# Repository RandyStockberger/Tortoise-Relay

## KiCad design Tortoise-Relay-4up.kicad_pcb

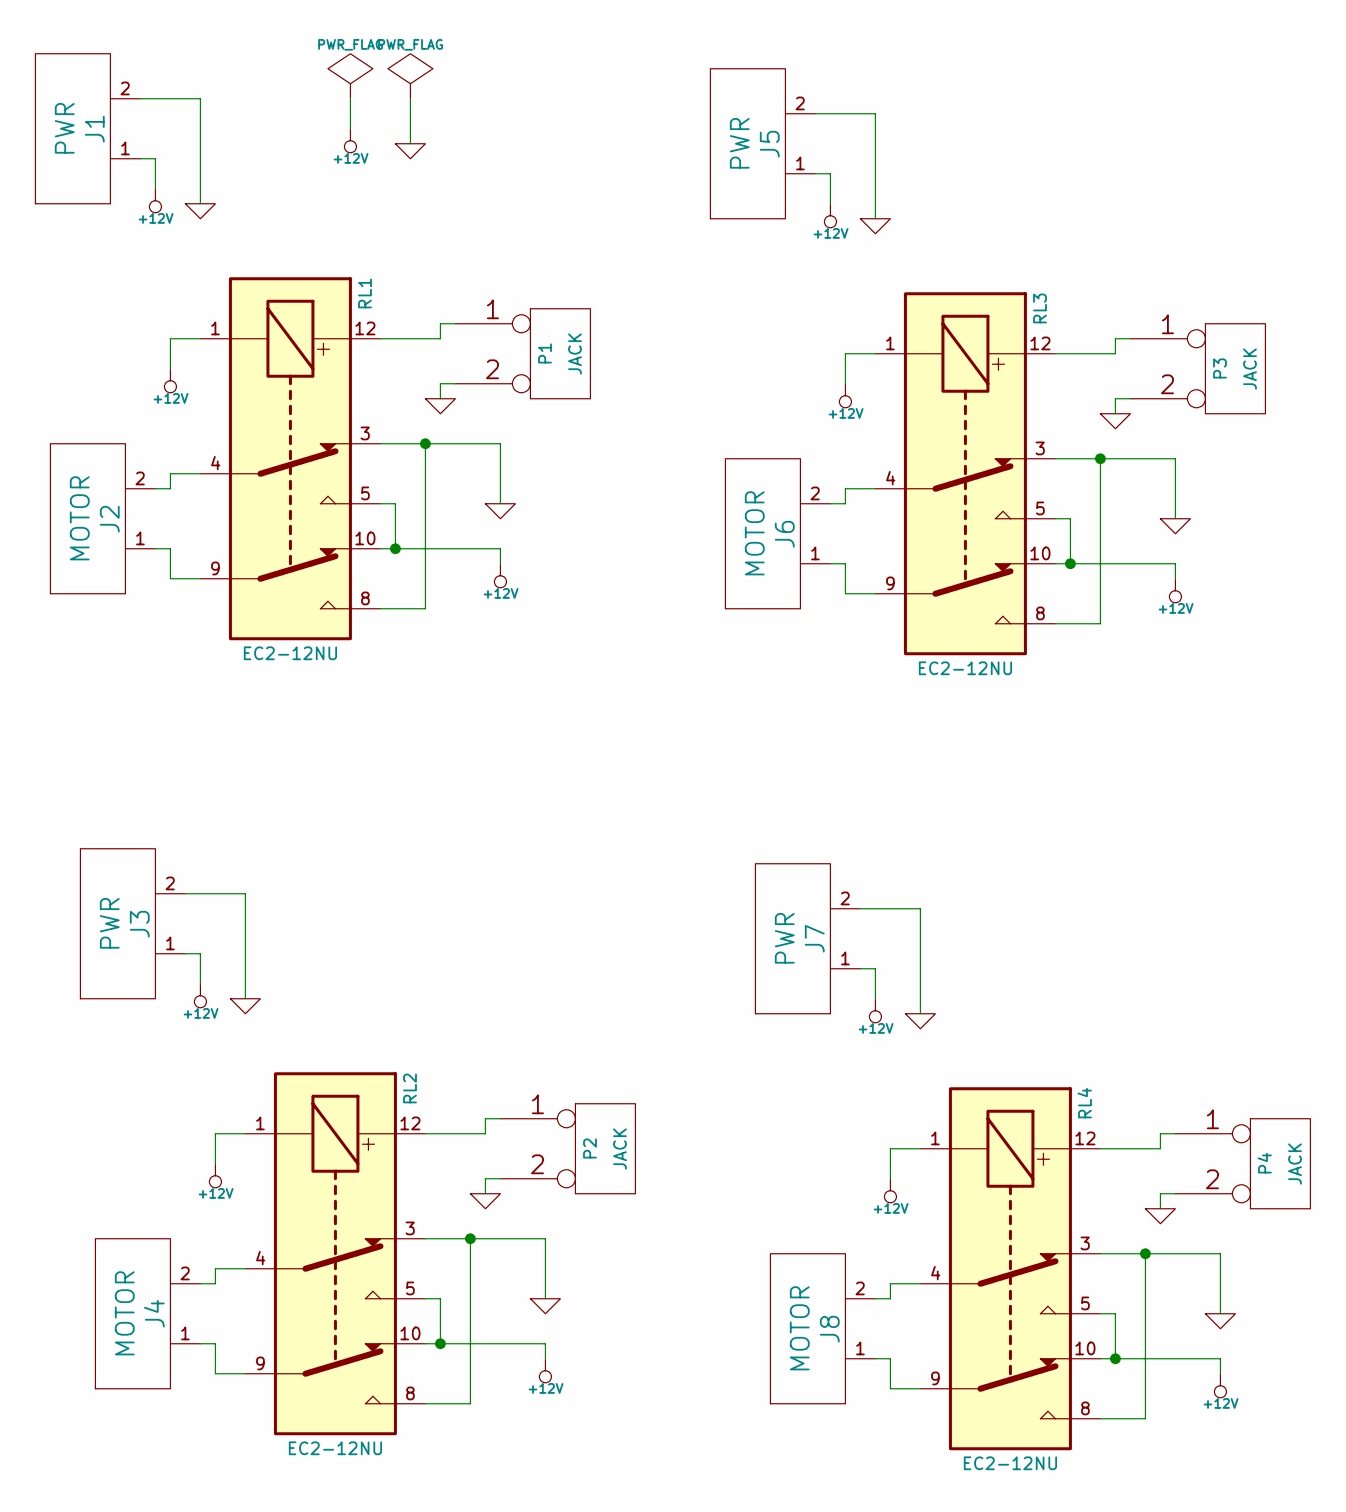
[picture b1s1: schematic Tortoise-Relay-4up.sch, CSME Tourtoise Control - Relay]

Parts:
J1, J3, J5, J7: PWR
J2, J4, J6, J8: MOTOR
P1, P2, P3, P4: JACK
RL1, RL2, RL3, RL4: EC2-12NU

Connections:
+12V: J1.1, J3.1, J5.1, J7.1, RL1.1, RL1.5, RL1.10, RL2.1, RL2.5, RL2.10, RL3.1, RL3.5, RL3.10, RL4.1, RL4.5, RL4.10
GND: J1.2, J3.2, J5.2, J7.2, P1.2 (PM), P2.2 (PM), P3.2 (PM), P4.2 (PM), RL1.3, RL1.8, RL2.3, RL2.8, RL3.3, RL3.8, RL4.3, RL4.8
unnamed: J8.1, RL4.9
unnamed: J8.2, RL4.4
unnamed: P4.1, RL4.12
unnamed: J4.1, RL2.9
unnamed: J4.2, RL2.4
unnamed: P2.1, RL2.12
unnamed: J6.1, RL3.9
unnamed: J6.2, RL3.4
unnamed: P3.1, RL3.12
unnamed: P1.1, RL1.12
unnamed: J2.1, RL1.9
unnamed: J2.2, RL1.4

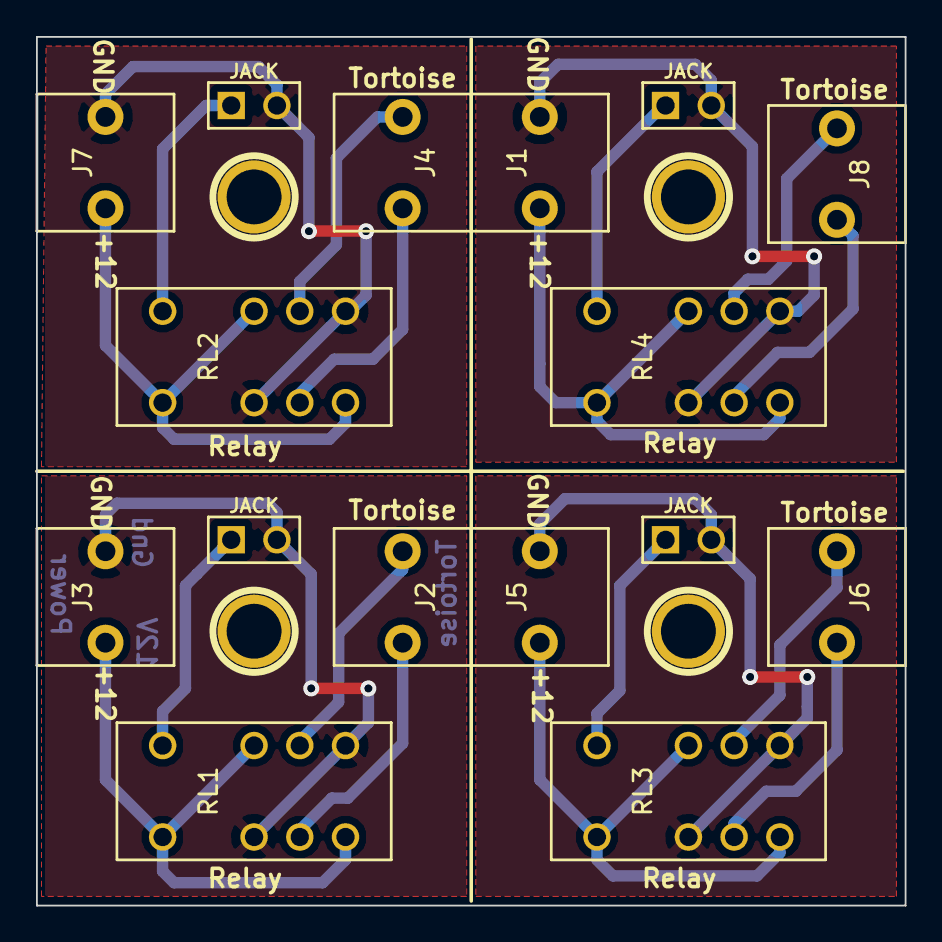
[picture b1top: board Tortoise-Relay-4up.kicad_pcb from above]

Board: 2 copper layers, 48.3 x 48.3 mm, 20 parts (0 on the bottom side), 14 nets.

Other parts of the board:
1PIN, 1PIN#2, 1PIN#3, 1PIN#4: P***; 1pin

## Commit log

2015-02-03 Initial version of tortoise relay panel in 4-up configuration
